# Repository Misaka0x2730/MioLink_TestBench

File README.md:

# MioLink TestBench

A hardware-in-the-loop bench for automated testing of the
[MioLink](https://github.com/Misaka0x2730/MioLink) debug probe.

The bench builds probe firmware and target test firmware, flashes both onto
real hardware, and runs a suite of functional tests over the physically wired
interfaces (SWD/JTAG, UART, RTT, SWO).

## How it works

A full run consists of three phases orchestrated by [`bench_run_all.sh`](scripts/bench_run_all.sh):

1. **Build probe firmware** ([`miolink_build_all.sh`](scripts/miolink_build_all.sh)) — builds
   every MioLink variant listed in the bench config and stages the `.uf2` images.
2. **Build target firmware** ([`targets_build_all.sh`](scripts/targets_build_all.sh)) —
   builds the `test_board` fixtures for each target platform and CLI backend.
3. **Run tests** ([`bench_run_tests_only.sh`](scripts/bench_run_tests_only.sh)) — flashes the
   probes and targets, verifies probe identity, and runs the tests.

Each script can also be run on its own if you only need a single phase.

## Bench configuration

The physical layout is described by a YAML file under [`config/`](config/): a
flat list of slots where each probe ↔ target pair carries everything needed —
probe serial number, target model, platform, wired interfaces, Vtref mode, SWO
presence, the set of CLI backends, and so on. Every field is documented inline
in the file.

A bench is fully described by its config, so you can keep one per physical setup
and select it with `--config` (the scripts default to
[`config/bench_pizero2w.yaml`](config/bench_pizero2w.yaml)).

## Repository layout

| Directory | Purpose |
|---|---|
| [`firmware/`](firmware/) | Test target firmware (`test_board`); platforms: `stm32f030`, `stm32f103`, `stm32f401`, `hc32f460` |
| [`scripts/cmake/`](scripts/cmake/) | Project-agnostic CMake build driver |
| [`scripts/miolink/`](scripts/miolink/) | Build, flash, and discovery of the MioLink probe (DFU detach / picotool) |
| [`scripts/usbutil/`](scripts/usbutil/) | Generic USB device lookup by VID/PID/serial |
| [`scripts/targets/`](scripts/targets/) | Target firmware builds and target control over GDB/BMP (`gdb`) |
| [`scripts/bench/`](scripts/bench/) | Bench runner and config parser |
| [`scripts/tests/`](scripts/tests/) | Functional tests: `uart`, `rtt`, `swo`, `buffer` |
| [`scripts/runner/`](scripts/runner/) | Self-hosted CI runner provisioning |
| `scripts/*.sh` | Entry-point wrappers from `scripts/`: `bench_run_all`, `bench_run_tests_only`, `miolink_build_all`, `targets_build_all` |
| [`hardware/`](hardware/) | KiCad adapter boards for WeAct Core Boards (STM32F1/F4, MSPM0G3507, STM32G0/C0) |
| [`config/`](config/) | Bench description YAMLs |

## Target platforms

The `test_board` firmware is built for several MCUs that cover different
Cortex-M cores: STM32F030 (CM0), STM32F103 (CM3), STM32F401 (CM4),
HC32F460 (CM4). Variants differ by CLI backend (UART / RTT / disabled),
SWO presence, and build type (Debug / Release).

## Getting started

### Prerequisites

- **ARM GNU Toolchain, CMake, Ninja** — for building the firmware (not needed on
  a bench host that only flashes and tests).
- **Python 3** with the packages from
  [`scripts/requirements.txt`](scripts/requirements.txt) (`pyusb`, `pygdbmi`,
  `pyserial`, `PyYAML`).
- **Git submodules** from [`.gitmodules`](.gitmodules) (CMSIS, STM32 HAL drivers,
  SEGGER RTT, embedded-cli) — pulled in by the clone step below.

### Setup

Clone the repository with its submodules:

```bash
git clone --recurse-submodules https://github.com/Misaka0x2730/MioLink_TestBench.git
cd MioLink_TestBench
```

If you already cloned without `--recurse-submodules`:

```bash
git submodule update --init --recursive
```

Install the Python dependencies:

```bash
pip install -r scripts/requirements.txt
```

## Usage

Run scripts from the repository root.

**Full run** — build probe firmware, build target firmware, flash, and test:

```bash
./scripts/bench_run_all.sh --miolink-firmware-root /path/to/MioLink/firmware
```

**Build only** — skip the flash-and-test phase:

```bash
./scripts/bench_run_all.sh --miolink-firmware-root /path/to/MioLink/firmware --build-only
```

**Run only** — reuse already-built images, just flash and test:

```bash
./scripts/bench_run_all.sh --run-only
```

**Individual phases:**

```bash
# 1. Build the MioLink probe .uf2 images
./scripts/miolink_build_all.sh --miolink-firmware-root /path/to/MioLink/firmware

# 2. Build the test_board target firmware
./scripts/targets_build_all.sh

# 3. Flash everything and run the tests
./scripts/bench_run_tests_only.sh
```

**Useful options** (anything after `--` is forwarded to the bench runner):

```bash
# Run a single probe by serial number
./scripts/bench_run_tests_only.sh -- --probe E66394664F387030

# Include slots marked enabled: false in the config
./scripts/bench_run_tests_only.sh -- --include-disabled

# Skip re-flashing the target firmware
./scripts/bench_run_tests_only.sh -- --no-target-flash

# Use a custom bench config
./scripts/bench_run_all.sh --config config/bench_pizero2w.yaml --miolink-firmware-root /path/to/MioLink/firmware
```

Pass `-h` / `--help` to any script for the full list of flags.

## CI/CD

There are two GitHub Actions workflows: one that purely builds the target
firmware, and one that runs the full hardware-in-the-loop bench.

### Build Test Firmware CI

[`build-test-firmware-ci.yml`](.github/workflows/build-test-firmware-ci.yml)
runs on every push and pull request to `main` (and on manual
`workflow_dispatch`). It compiles the `test_board` firmware for the **full
variant matrix** and packages the results, acting as a compile-only smoke test
that nothing has broken across platforms/configs.

- **`version` job** — derives one version string shared by every artifact name
  (git tag name for tag refs, otherwise the short SHA) so the build matrix and
  the packaging job stay consistent.
- **`build` job (matrix)** — a matrix over the variant axes: target platform,
  `CONFIG_CLI` (`UART` / `RTT` / `NONE`), `CONFIG_TEST_SWO` (`OFF` / `ON`), and
  build type (`Debug` / `Release`). Combinations a platform can't support are
  excluded (e.g. SWO on a Cortex-M0 with no ITM/TPIU). `fail-fast` is off, so one
  broken variant doesn't hide the rest. Each cell checks out submodules, sets up
  the ARM GCC toolchain, extracts any committed vendor SDK the platform needs,
  runs `cmake` configure + build, and uploads a version-stamped `.elf` artifact.
- **`package` job** — runs only if **all** matrix builds succeeded (so the
  archive is never silently incomplete), merges every per-variant ELF into a
  single `MioLink_TestBench_firmware_<version>` archive, and best-effort prunes
  the intermediate `elf-*` staging artifacts.

### Run Bench CI

[`run-bench-ci.yml`](.github/workflows/run-bench-ci.yml) runs the actual bench
on physical hardware. It is triggered by **`repository_dispatch`
(`miolink-build`)** from the MioLink build pipeline once that pipeline has built
the probe firmware — or manually via `workflow_dispatch` with a `run_id` (and an
optional `sha` to report on).

The flow is split so the physical bench host stays cheap (it never compiles):

1. **`build-fixtures` job** (GitHub-hosted) — builds the `test_board` fixtures
   in the exact layout `run_bench.py` expects
   (`firmware/build/cli-X_swo-Y/test_boards/...`) and uploads only the `.elf`
   files as a `target-fixtures` artifact. The self-hosted runner therefore never
   needs a toolchain.
2. **`bench` job** (self-hosted, labels `[self-hosted, miolink-bench]`) — the
   one with the real hardware (e.g. a Pi Zero 2W):
   - Resolves the MioLink `run_id` from the dispatch payload or manual input.
   - **Cross-repo downloads** the exact probe `.uf2` set that this MioLink run
     produced (`actions/download-artifact` with `repository: Misaka0x2730/MioLink`
     + `run-id`, authenticated with the `MIOLINK_BENCH_TOKEN` secret). This
     guarantees the bench tests the precise artifacts that triggered it.
   - Downloads and unpacks the `target-fixtures` from step 1, installs the
     runtime-only Python deps, and runs `scripts/bench_run_tests_only.sh` to
     flash and test against the bench config.
   - A `concurrency` group (`cancel-in-progress: false`) serializes runs so
     concurrent MioLink changes **queue** instead of fighting over the single
     physical bench.
3. **`report` job** — `if: always()`, so it runs even when the bench fails or is
   skipped. It posts a commit status (`context: miolink-bench`) back onto the
   MioLink commit SHA, which renders in MioLink's PR checks list and resolves the
   pending status MioLink had set. It no-ops when there is no SHA to report on
   (e.g. a manual run without the `sha` input).

Both the cross-repo artifact download and the status report authenticate with
the **`MIOLINK_BENCH_TOKEN`** repository secret — a token with read access to
the MioLink repo's Actions artifacts and write access to its commit statuses.
The workflow cannot fetch the probe firmware or report results without it.

In other words, the two repos form a loop: **MioLink builds probe firmware →
dispatches to this repo → the bench flashes and tests it on real targets →
the result is reported back as a check on the MioLink commit.**

### Self-hosted bench runner

The `bench` job lands on a self-hosted runner labelled
`[self-hosted, miolink-bench]` — the host physically wired to the probes and
targets. Because compilation happens on GitHub-hosted runners, this host only
flashes and tests, so a low-powered SBC (e.g. a Raspberry Pi / Pi Zero 2W
running DietPi) is enough.

[`scripts/runner/provision_ghrunner.sh`](scripts/runner/provision_ghrunner.sh)
provisions such a host from scratch. It installs exactly what
`scripts/bench/run_bench.py` needs at job time — `arm-none-eabi-gdb` (flashes
targets over the BMP GDB/MI server), `picotool` (BOOTSEL flashing of RP2 probes,
incl. RP2350 / Pico 2W), `dfu-util` (detaches a running probe into BOOTSEL), and
`python3` + libusb for the runtime deps — plus udev rules and group membership
so an unprivileged service user gets raw-USB and `/dev/ttyACM*` access. It then
registers the GitHub Actions runner under a dedicated `ghrunner` user and
installs it as an auto-starting systemd service.

Run it on the Pi (it re-execs itself with `sudo`):

```bash
sudo ./scripts/runner/provision_ghrunner.sh \
    --toolchain-url <ARM_GNU_TOOLCHAIN_TARBALL_URL> \
    --token         <GITHUB_RUNNER_REGISTRATION_TOKEN> \
    --labels        miolink-bench \
    --url           https://github.com/Misaka0x2730/MioLink_TestBench
```

The `--labels` value must include `miolink-bench` so the `bench` job targets
this host.

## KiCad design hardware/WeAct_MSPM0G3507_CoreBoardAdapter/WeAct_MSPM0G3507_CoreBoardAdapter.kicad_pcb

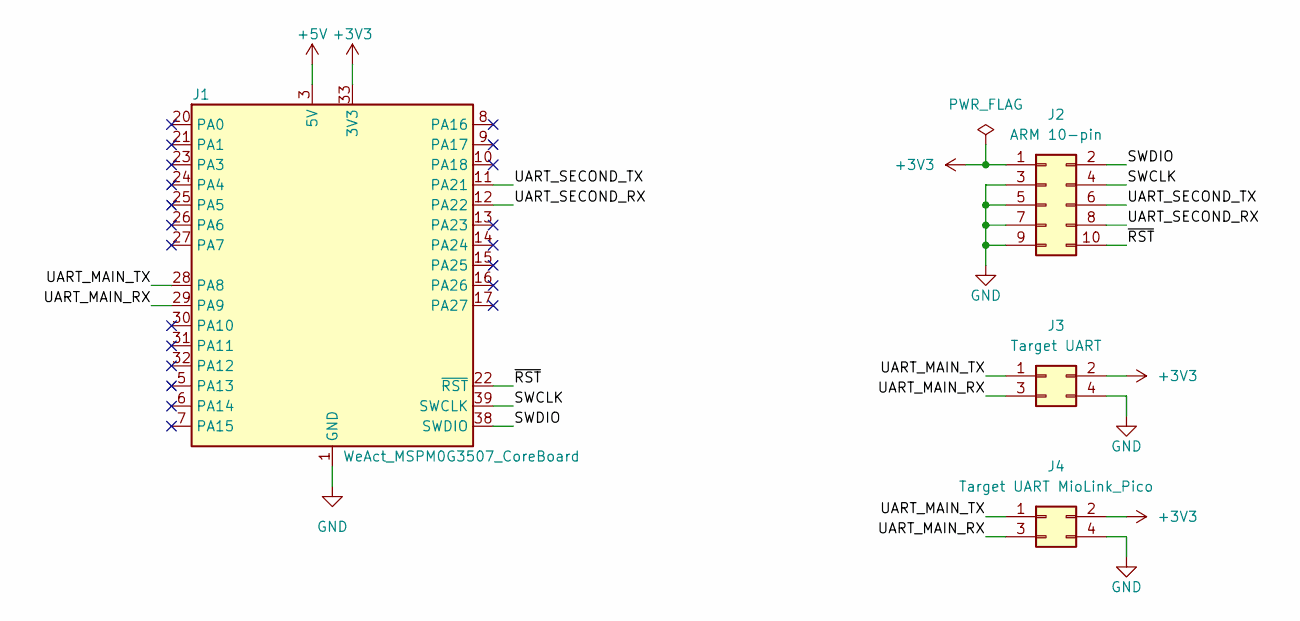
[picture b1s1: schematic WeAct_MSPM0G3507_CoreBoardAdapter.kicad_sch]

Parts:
J1: WeAct_MSPM0G3507_CoreBoard
J2: ARM 10-pin; PinSocket_2x05_P2.54mm_Horizontal
J3: Target UART; PinSocket_2x02_P2.54mm_Horizontal
J4: Target UART MioLink_Pico; PinSocket_2x02_P2.54mm_Horizontal

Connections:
+3V3: J1.33 (3V3), J1.34 (3V3), J1.37 (3V3), J2.1, J3.2, J4.2
+5V: J1.3 (5V), J1.4 (5V)
/SWCLK: J1.39 (SWCLK), J2.4
/SWDIO: J1.38 (SWDIO), J2.2
/UART_MAIN_RX: J1.29 (PA9), J3.3, J4.3
/UART_MAIN_TX: J1.28 (PA8), J3.1, J4.1
/UART_SECOND_RX: J1.12 (PA22), J2.8
/UART_SECOND_TX: J1.11 (PA21), J2.6
/~RST: J1.22 (~RST), J2.10
GND: J1.1 (GND), J1.2 (GND), J1.18 (GND), J1.19 (GND), J1.35 (GND), J1.36 (GND), J1.40 (GND), J2.3, J2.5, J2.7, J2.9, J3.4, J4.4

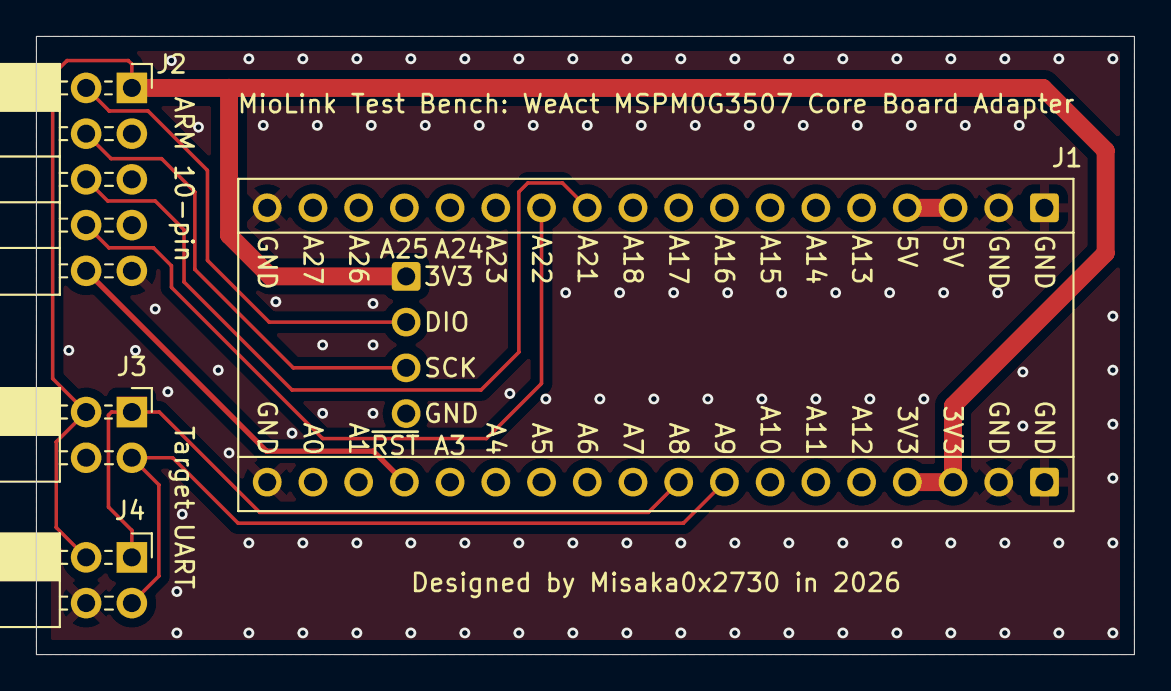
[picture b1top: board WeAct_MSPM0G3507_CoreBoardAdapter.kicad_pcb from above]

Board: 2 copper layers, 61.0 x 34.3 mm, 5 parts (1 on the bottom side), 10 nets.

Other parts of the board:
G1: PROJECT PAGE; LOGO

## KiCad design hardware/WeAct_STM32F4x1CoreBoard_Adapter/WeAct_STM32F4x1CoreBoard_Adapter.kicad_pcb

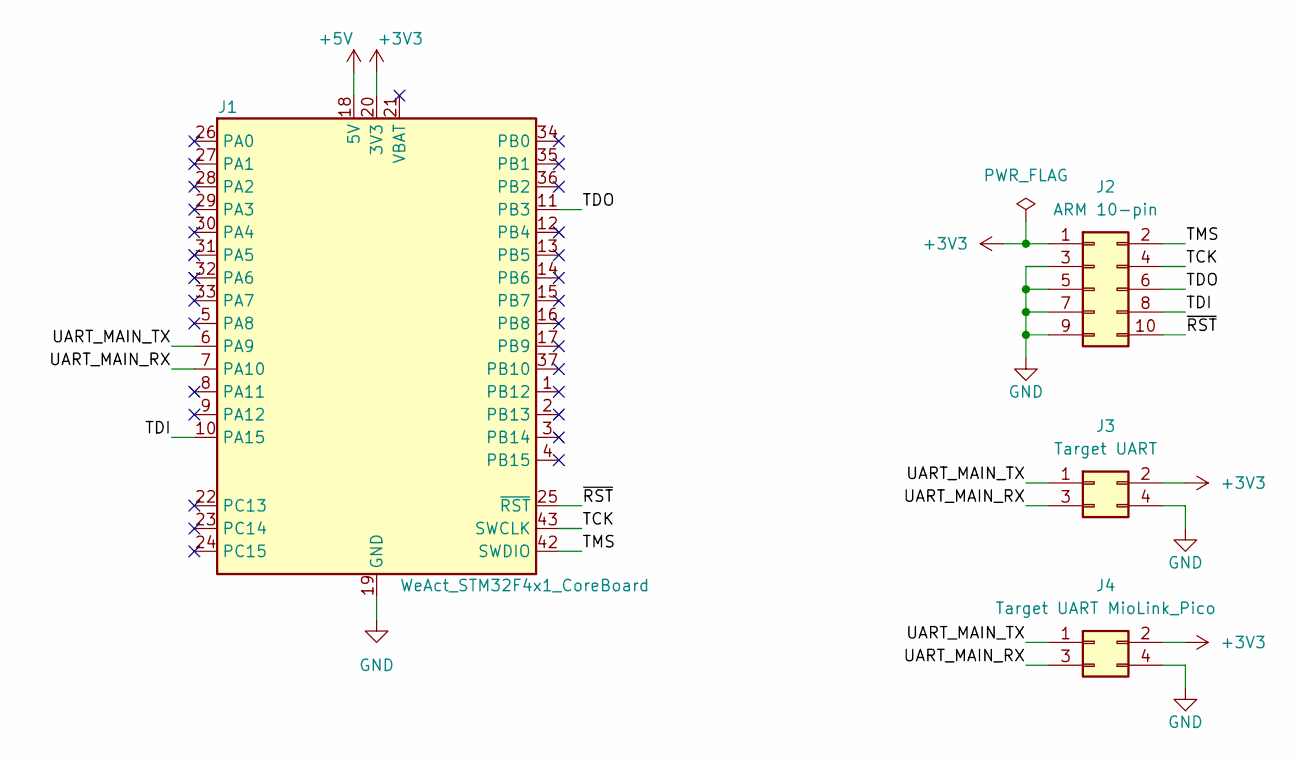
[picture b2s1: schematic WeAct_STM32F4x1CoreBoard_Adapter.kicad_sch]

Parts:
J1: WeAct_STM32F4x1_CoreBoard
J2: ARM 10-pin; PinSocket_2x05_P2.54mm_Horizontal
J3: Target UART; PinSocket_2x02_P2.54mm_Horizontal
J4: Target UART MioLink_Pico; PinSocket_2x02_P2.54mm_Horizontal

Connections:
+3V3: J1.20 (3V3), J1.38 (3V3), J1.41 (3V3), J2.1, J3.2, J4.2
+5V: J1.18 (5V), J1.40 (5V)
/TCK: J1.43 (SWCLK), J2.4
/TDI: J1.10 (PA15), J2.8
/TDO: J1.11 (PB3), J2.6
/TMS: J1.42 (SWDIO), J2.2
/UART_MAIN_RX: J1.7 (PA10), J3.3, J4.3
/UART_MAIN_TX: J1.6 (PA9), J3.1, J4.1
/~RST: J1.25 (~RST), J2.10
GND: J1.19 (GND), J1.39 (GND), J1.44 (GND), J2.3, J2.5, J2.7, J2.9, J3.4, J4.4

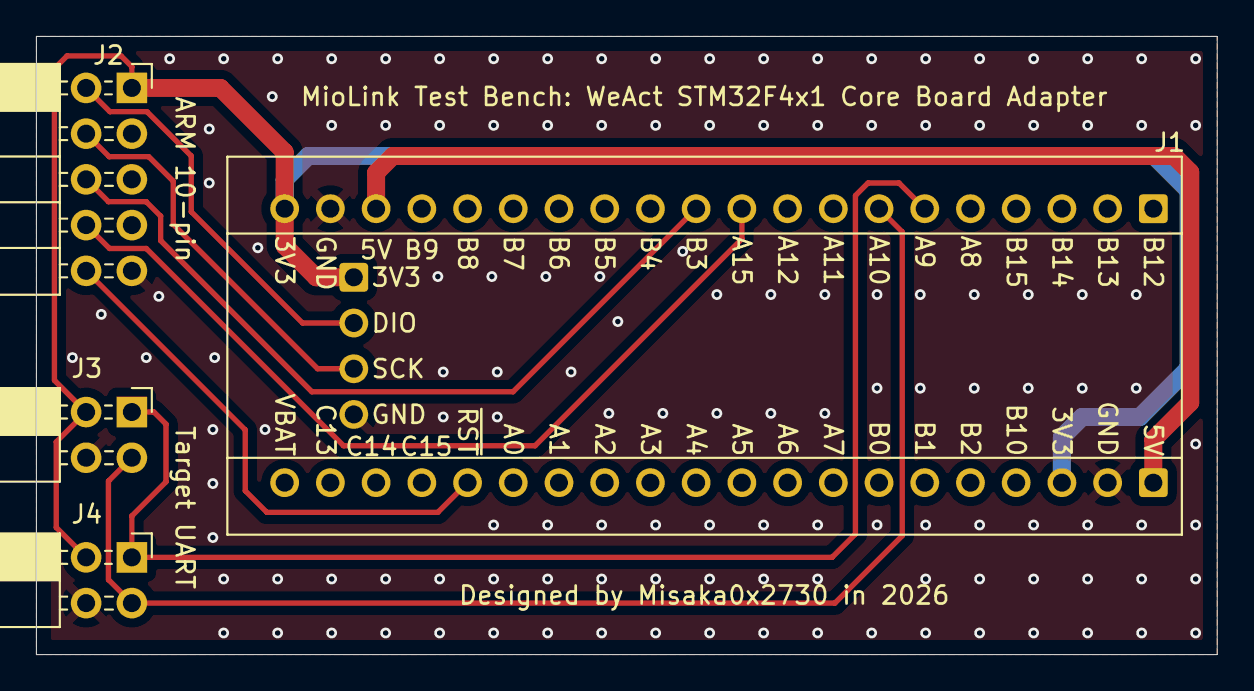
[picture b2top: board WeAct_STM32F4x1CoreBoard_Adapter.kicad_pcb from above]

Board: 2 copper layers, 65.6 x 34.3 mm, 5 parts (1 on the bottom side), 10 nets.

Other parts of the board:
G1: PROJECT PAGE; LOGO

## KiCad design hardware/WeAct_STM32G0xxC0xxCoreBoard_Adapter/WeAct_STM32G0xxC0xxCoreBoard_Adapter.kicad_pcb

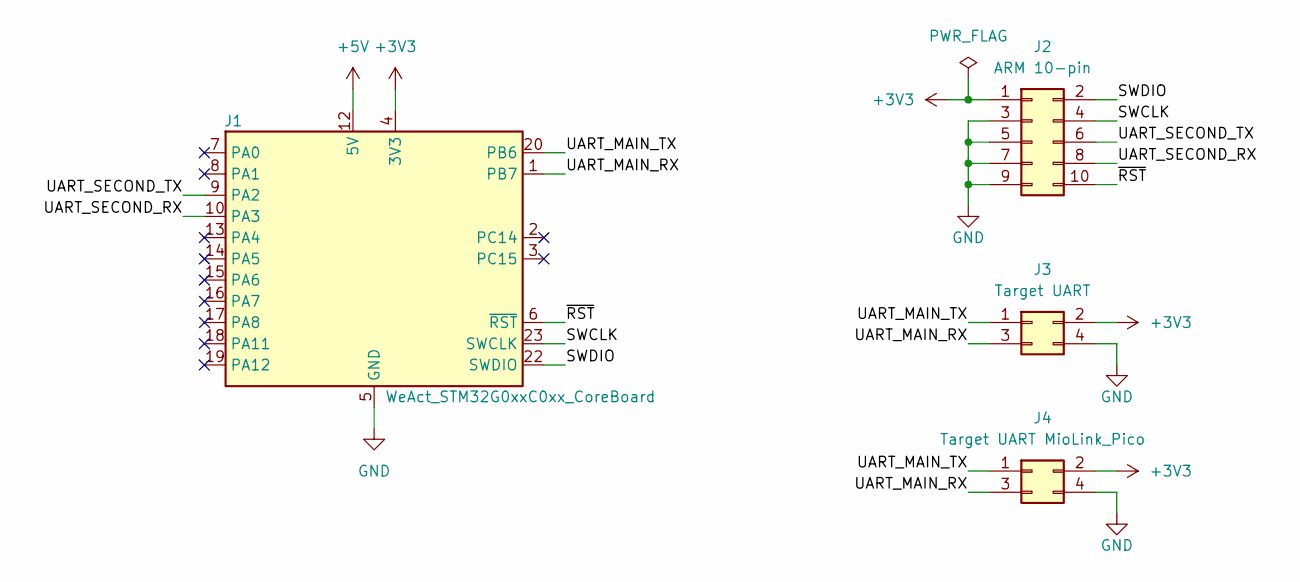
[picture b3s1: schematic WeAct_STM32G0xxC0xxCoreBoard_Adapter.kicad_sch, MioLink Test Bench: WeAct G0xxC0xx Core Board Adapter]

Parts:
J1: WeAct_STM32G0xxC0xx_CoreBoard
J2: ARM 10-pin; PinSocket_2x05_P2.54mm_Horizontal
J3: Target UART; PinSocket_2x02_P2.54mm_Horizontal
J4: Target UART MioLink_Pico; PinSocket_2x02_P2.54mm_Horizontal

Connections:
+3V3: J1.4 (3V3), J1.21 (3V3), J2.1, J3.2, J4.2
+5V: J1.12 (5V)
/SWCLK: J1.23 (SWCLK), J2.4
/SWDIO: J1.22 (SWDIO), J2.2
/UART_MAIN_RX: J1.1 (PB7), J3.3, J4.3
/UART_MAIN_TX: J1.20 (PB6), J3.1, J4.1
/UART_SECOND_RX: J1.10 (PA3), J2.8
/UART_SECOND_TX: J1.9 (PA2), J2.6
/~RST: J1.6 (~RST), J2.10
GND: J1.5 (GND), J1.11 (GND), J1.24 (GND), J2.3, J2.5, J2.7, J2.9, J3.4, J4.4

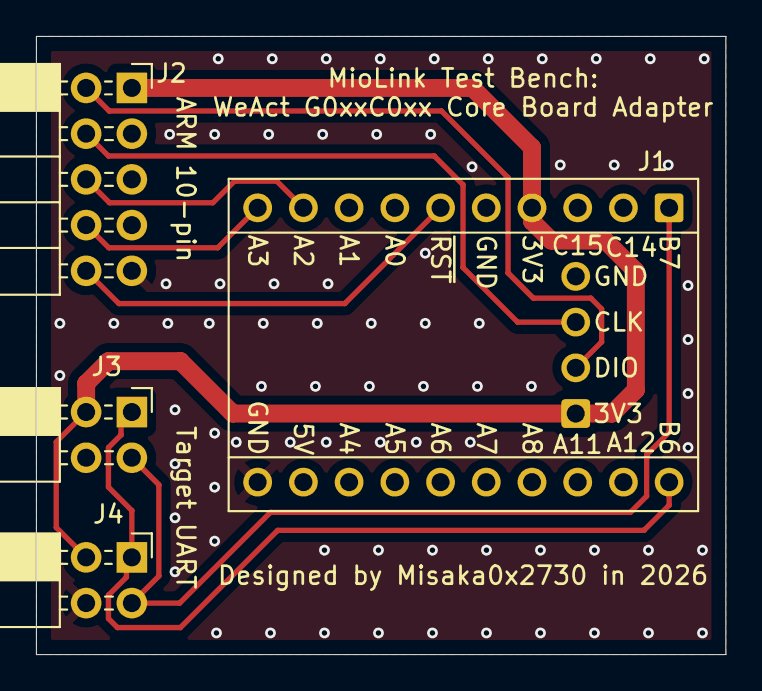
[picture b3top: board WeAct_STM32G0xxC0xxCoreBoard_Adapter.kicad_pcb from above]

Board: 2 copper layers, 38.3 x 34.3 mm, 5 parts (1 on the bottom side), 9 nets.

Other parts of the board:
G1: PROJECT PAGE; LOGO

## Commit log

2026-03-17 Initial commit, added stm32f103 and stm32f401 test platforms
2026-05-29 Implemented test scripts, added STM32F030 and HC32F460 platforms
2026-05-29 Fixed HC32F460 DDL archive
2026-05-30 Fixed path in _find_mount_linux
2026-05-30 Updated CI/CD, build and bench scripts refactoring
2026-05-30 Use --break-system-packages for initial tests
2026-05-31 Build test firmwares on Github runner
2026-05-31 Create separate script for freq_parse
2026-06-01 Use copyfile for .uf2 image instead of copy
2026-06-01 Use picotool to flash MioLink
2026-06-01 Added retry mechanism for MioLink flashing
2026-06-01 Fixed problem with wrong RP2350 PID
2026-06-01 Created provisioning script for Github self-hosted runner
2026-06-01 Fixed toolchain installation - don't unpack the toolchain into /tmp folder
2026-06-01 Install picotool from apt instead of building from sources
2026-06-02 Removed freq_parse script
2026-06-06 Added KiCad files for adapter boards for MSPM0G3507, STM32F103, STM32F411 and STM32G030_F030
2026-06-06 Renamed project to MioLink_TestBench
2026-06-06 Renamed CI configs
2026-06-06 Updated bench config name
2026-06-08 Refactoring scripts, added README

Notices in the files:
hardware/WeAct_STM32G0xxC0xxCoreBoard_Adapter/WeAct_STM32G0xxC0xxCoreBoard_Adapter.kicad_sch:
License: CERN-OHL-P-2.0
